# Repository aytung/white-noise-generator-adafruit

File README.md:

# white-noise-generator-adafruit

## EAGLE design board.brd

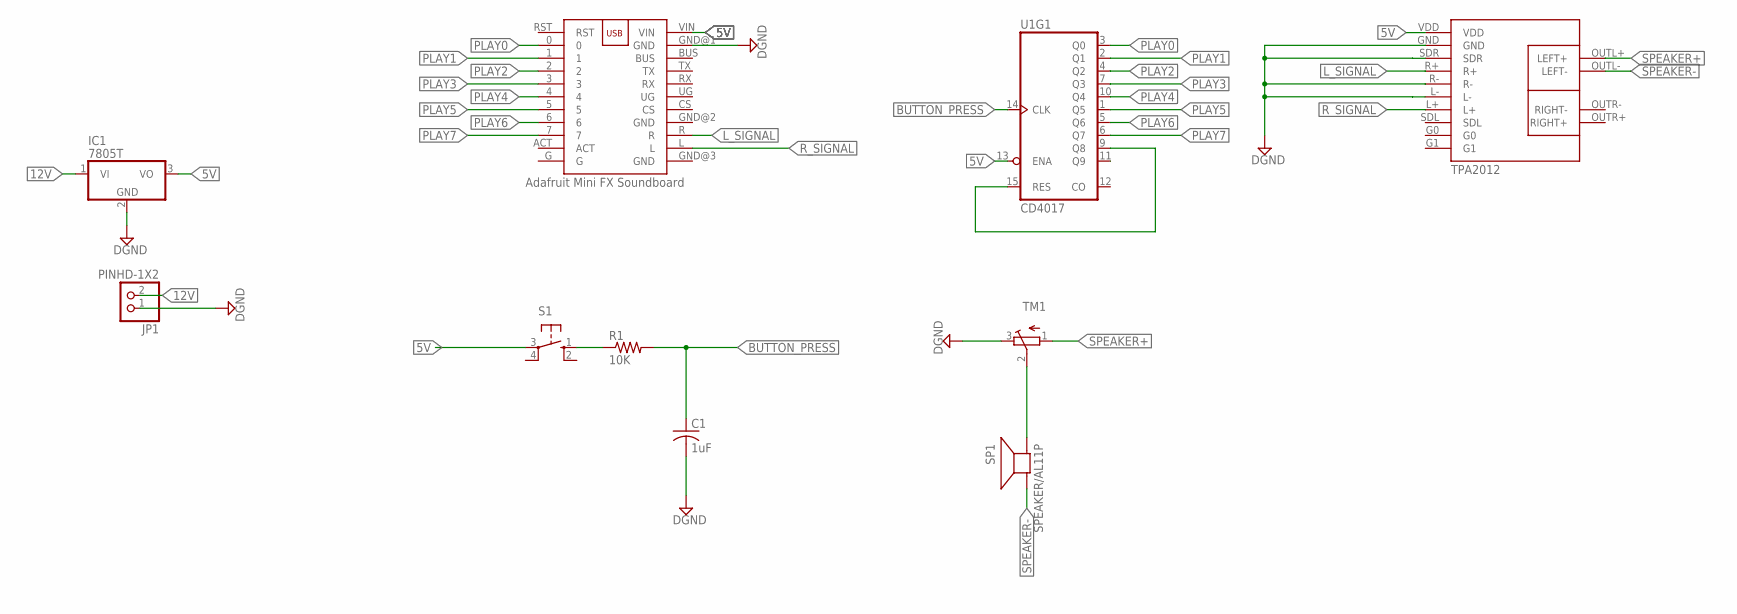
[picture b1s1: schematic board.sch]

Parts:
C1: 1uF; C025-050X050
IC1: 7805T; TO220H
JP1: PINHD-1X2; 1X02
R1: 10K; 0204/5
S1: 10-XX; B3F-10XX
SP1: SPEAKER/AL11P; AL11P
TM1: TRIMPOT3386; TRIM-3386
U1: CD4017; DIP16
U$1: TPA2012
U$2: ADAFRUIT_AUDIO_FX_MINI_SOUNDBOARD

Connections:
5V: IC1.3 (VO), S1.3, U1.13 (ENA), U$1.VDD, U$2.VIN
12V: IC1.1 (VI), JP1.2
BUTTON_PRESS: C1.1, R1.2, U1.14 (CLK)
DGND: C1.2, IC1.2 (GND), JP1.1, TM1.3 (E), U$1.GND, U$1.L-, U$1.R-, U$1.SDR, U$2.GND@1 (GND)
L_SIGNAL: U$1.R+, U$2.R
unnamed: U1.9 (Q8), U1.15 (RES)
unnamed: R1.1, S1.1 (S)
unnamed: SP1.+, TM1.2 (S)
PLAY0: U1.3 (Q0), U$2.0
PLAY1: U1.2 (Q1), U$2.1
PLAY2: U1.4 (Q2), U$2.2
PLAY3: U1.7 (Q3), U$2.3
PLAY4: U1.10 (Q4), U$2.4
PLAY5: U1.1 (Q5), U$2.5
PLAY6: U1.5 (Q6), U$2.6
PLAY7: U1.6 (Q7), U$2.7
R_SIGNAL: U$1.L+, U$2.L
SPEAKER+: TM1.1 (A), U$1.OUTL+ (LEFT+)
SPEAKER-: SP1.-, U$1.OUTL- (LEFT-)

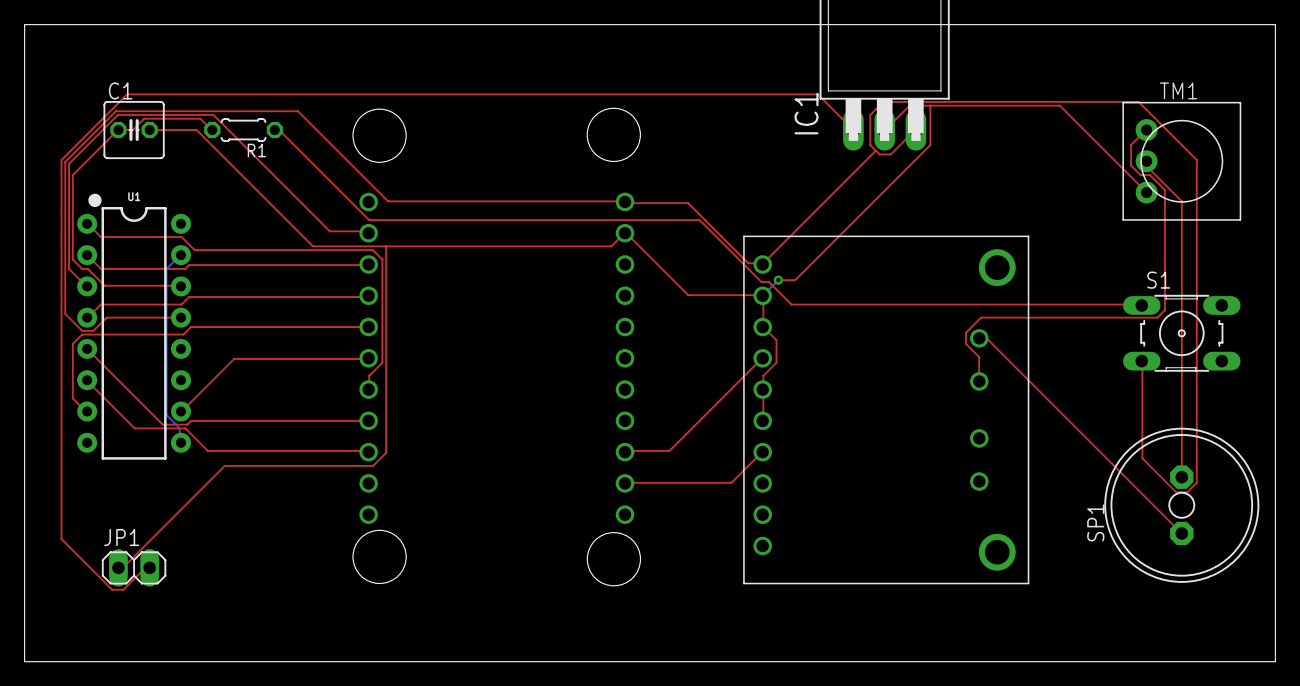
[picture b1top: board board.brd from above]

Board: 2 copper layers, 101.6 x 51.7 mm, 10 parts (0 on the bottom side), 19 nets.

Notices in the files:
parts and their libraries:
SparkFun-IC-Logic: Licensing: Creative Commons ShareAlike 4.0 International - https://creativecommons.org/licenses/by-sa/4.0
